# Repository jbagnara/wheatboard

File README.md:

# wheatboard

```bash
sudo pacman -Syu kicad
sudo pacman -Syu --asdeps kicad-library kicad-library-3d
```

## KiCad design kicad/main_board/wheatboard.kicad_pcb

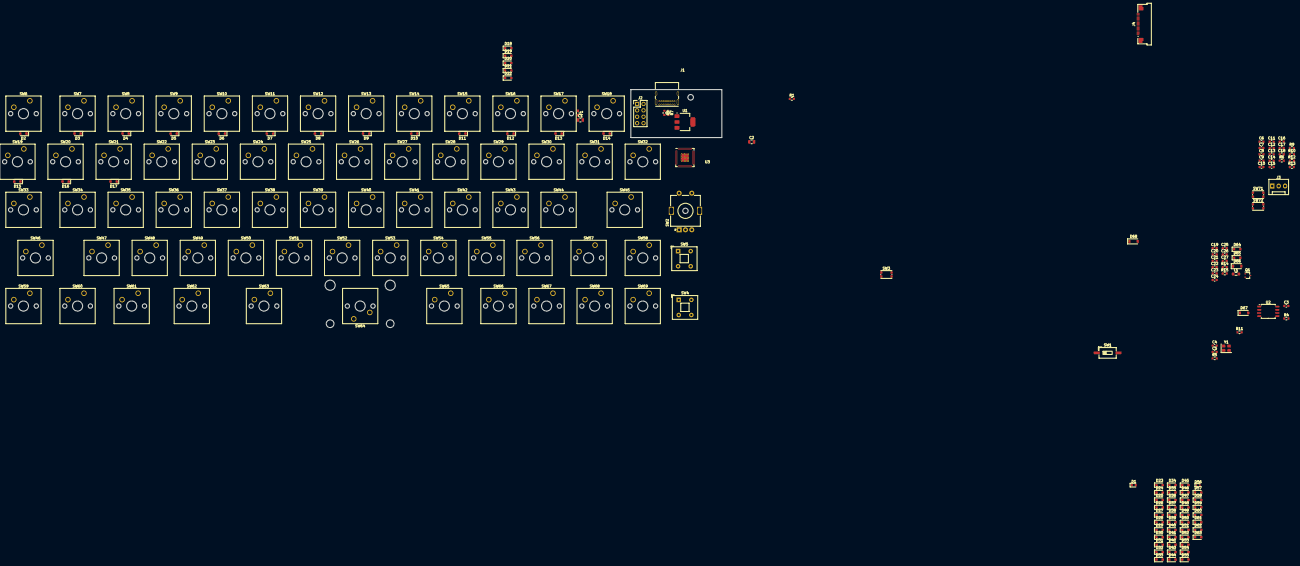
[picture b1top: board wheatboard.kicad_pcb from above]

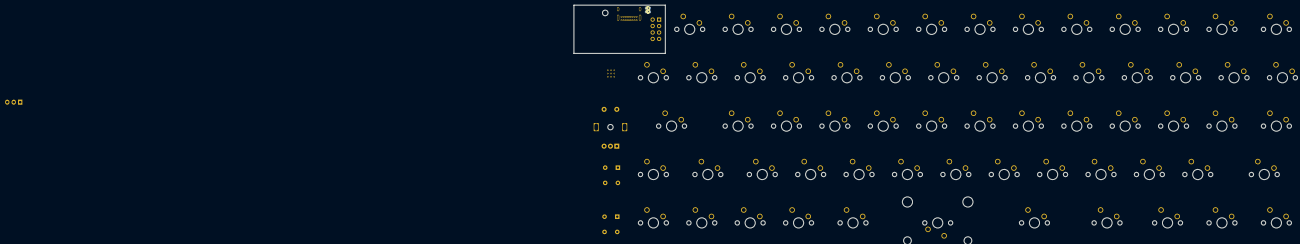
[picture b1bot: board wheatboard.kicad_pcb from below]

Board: 2 copper layers, 192 parts (2 on the bottom side), 132 nets, no tracks yet.

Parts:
C1, C2: 10u; C_0805_2012Metric
C3, C6, C7, C8, C9, C10, C11, C12, C13, C14, C17, C18: 100n; C_0603_1608Metric
C4, C5: 15p; C_0603_1608Metric
C15, C16, C19, C20, C21, C22, C23, C24, C26: 1u; C_0603_1608Metric
C25, C27: 4.7u; C_0603_1608Metric
D1: 3V3; LED_0603_1608Metric
D2, D3, D4, D5, D6, D7, D8, D9, D10, D11, D12, D13, D14, D15, D16, D17, D18, D19, D20, D21, D22, D23, D24, D25, D26, D27, D28, D29, D30, D31, D32, D33, D34, D35, D36, D37, D38, D39, D40, D41, D42, D43, D44, D45, D46, D47, D48, D49, D50, D51, D52, D53, D54, D55, D57, D58, D59, D60, D61, D62, D63, D64, D65: 1N4148WT; D_SOD-323_HandSoldering
D56: 1N4148WT; D_SOD-523
D66, D67, D68: MBR0530; D_SOD-123
F1: Fuse; Fuse_0603_1608Metric_Pad1.05x0.95mm_HandSolder
J1: USB_C_Receptacle_USB2.0_16P; USB_C_Receptacle_GCT_USB4085
J2: Conn_01x08; PinHeader_2x04_P2.54mm_Vertical
J3: SWD Debug; FanPinHeader_1x03_P2.54mm_Vertical
J4: Conn_01x18; Amphenol_F32Q-1A7x1-11018_1x18-1MP_P0.5mm_Horizontal
L1: 47u; L_0805_2012Metric_Pad1.05x1.20mm_HandSolder
Q1: Si1308EDL; SOT-323_SC-70
R1: 110; R_0603_1608Metric
R2, R3: 5.1k; R_0603_1608Metric
R4: DNF; R_0603_1608Metric
R5, R6: 1k; R_0603_1608Metric
R7, R8: 27; R_0603_1608Metric
R9, R10, R11, R12, R13: 10k; R_0603_1608Metric
R14: 1M; R_0603_1608Metric
R15: 2.2; R_0603_1608Metric
SW1: SW_DIP_x01; SW_DIP_SPSTx01_Slide_6.7x4.1mm_W8.61mm_P2.54mm_LowProfile
SW2: RotaryEncoder_Switch; RotaryEncoder_Alps_EC11E-Switch_Vertical_H20mm_MountingHoles
SW3, SW71, SW72: SW_Push; SW_Push_1P1T_NO_CK_KMR2
SW4: SW_Push; SW_Push_2P1T_Toggle_CK_PVA1xxH3xxxxxxV2
SW5: SW_Push; SW_Push_2P1T_Toggle_CK_PVA1xxH2xxxxxxV2
SW6, SW33, SW57, SW59, SW61, SW62, SW65: SW_Push; SW_Cherry_MX_1.25u_PCB
SW7, SW8, SW9, SW10, SW11, SW12, SW13, SW14, SW15, SW16, SW17, SW18, SW19, SW20, SW21, SW22, SW23, SW24, SW25, SW26, SW27, SW28, SW29, SW30, SW31, SW32, SW34, SW35, SW36, SW37, SW38, SW39, SW40, SW41, SW42, SW43, SW44, SW47, SW48, SW49, SW50, SW51, SW52, SW53, SW54, SW55, SW56, SW58, SW60, SW66, SW67, SW68, SW69: SW_Push; SW_Cherry_MX_1.00u_PCB
SW45, SW46, SW63: SW_Push; SW_Cherry_MX_1.75u_PCB
SW64: SW_Push; SW_Cherry_MX_2.25u_PCB
U1: NCP1117-3.3_SOT223; SOT-223-3_TabPin2
U2: W25Q128JVS; SOIC-8_5.3x5.3mm_P1.27mm
U3: RP2040; RP2040-QFN-56
Y1: ABM8-272-T3; Crystal_SMD_3225-4Pin_3.2x2.5mm

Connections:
+1V1: C6.1, C7.1, C15.1, U3.23 (DVDD), U3.45 (VREG_VOUT), U3.50 (DVDD)
+3V3: C2.1, C3.1, C8.1, C9.1, C10.1, C11.1, C12.1, C13.1, C14.1, C16.1, C27.1, J4.10, L1.1, R1.1, R4.1, R9.1, R10.1, R11.1, R12.1, R13.1, U1.2 (VO), U2.8 (VCC), U3.1 (IOVDD), U3.10 (IOVDD), U3.22 (IOVDD), U3.33 (IOVDD), U3.42 (IOVDD), U3.43 (ADC_AVDD), U3.44 (VREG_IN), U3.48 (USB_VDD), U3.49 (IOVDD)
/Flash/~USB_BOOT: R5.2, SW1.2
/MCU/RUN: R11.2, SW3.1, U3.26 (RUN)
/MCU/SWCLK: J3.3, U3.24 (SWCLK)
/MCU/SWD: J3.1, U3.25 (SWD)
Col0: D2.1 (K), D15.1 (K), D29.1 (K), D42.1 (K), D55.1 (K), U3.18 (GPIO15)
Col1: D3.1 (K), D16.1 (K), D30.1 (K), D56.1 (K), U3.17 (GPIO14)
Col2: D4.1 (K), D17.1 (K), D31.1 (K), D43.1 (K), D57.1 (K), U3.16 (GPIO13)
Col3: D5.1 (K), D18.1 (K), D32.1 (K), D44.1 (K), U3.15 (GPIO12)
Col4: D6.1 (K), D19.1 (K), D33.1 (K), D45.1 (K), D58.1 (K), U3.14 (GPIO11)
Col5: D7.1 (K), D20.1 (K), D34.1 (K), D46.1 (K), D59.1 (K), U3.13 (GPIO10)
Col6: D8.1 (K), D21.1 (K), D35.1 (K), D47.1 (K), U3.12 (GPIO9)
Col7: D9.1 (K), D22.1 (K), D36.1 (K), D48.1 (K), D60.1 (K), U3.11 (GPIO8)
Col8: D10.1 (K), D23.1 (K), D37.1 (K), D49.1 (K), U3.9 (GPIO7)
Col9: D11.1 (K), D24.1 (K), D38.1 (K), D50.1 (K), D61.1 (K), U3.8 (GPIO6)
Col10: D12.1 (K), D25.1 (K), D39.1 (K), D51.1 (K), D62.1 (K), U3.7 (GPIO5)
Col11: D13.1 (K), D26.1 (K), D40.1 (K), D52.1 (K), D63.1 (K), U3.6 (GPIO4)
Col12: D14.1 (K), D27.1 (K), D41.1 (K), D53.1 (K), D64.1 (K), U3.5 (GPIO3)
Col13: D28.1 (K), D54.1 (K), D65.1 (K), U3.4 (GPIO2)
DISPLAY_D/C: J4.6, U3.31 (GPIO20)
DISPLAY_GDR: J4.1, Q1.1 (G), R14.1
DISPLAY_PREVGH: C26.1, D68.1 (K), J4.15
DISPLAY_PREVGL: C24.1, D66.2 (A), J4.17
DISPLAY_RESE: J4.2, Q1.2 (S), R15.1
GND: C1.2, C2.2, C3.2, C4.2, C5.2, C6.2, C7.2, C8.2, C9.2, C10.2, C11.2, C12.2, C13.2, C14.2, C15.2, C16.2, C17.2, C18.2, C19.2, C20.1, C21.1, C22.1, C23.1, C24.2, C26.2, C27.2, D1.1 (K), D67.1 (K), J1.A1 (GND), J1.A12 (GND), J1.B1 (GND), J1.B12 (GND), J1.S1 (SHIELD), J3.2, J4.11, R2.2, R3.1, R14.2, R15.2, SW1.1, SW2.C, SW2.S2, SW3.2, SW4.2, SW5.2, SW71.2, SW72.2, U1.1 (GND), U2.4 (GND), U3.19 (TESTEN), U3.57 (GND), Y1.2, Y1.4
unnamed: C5.1, R6.2, Y1.3
unnamed: D1.2 (A), R1.2
unnamed: D2.2 (A), SW6.2
unnamed: D3.2 (A), SW7.2
unnamed: D4.2 (A), SW8.2
unnamed: D5.2 (A), SW9.2
unnamed: D6.2 (A), SW10.2
unnamed: D7.2 (A), SW11.2
unnamed: D8.2 (A), SW12.2
unnamed: D9.2 (A), SW13.2
unnamed: D10.2 (A), SW14.2
unnamed: D11.2 (A), SW15.2
unnamed: D12.2 (A), SW16.2
unnamed: D13.2 (A), SW17.2
unnamed: D14.2 (A), SW18.2
unnamed: D15.2 (A), SW19.2
unnamed: D16.2 (A), SW20.2
unnamed: D17.2 (A), SW21.2
unnamed: D18.2 (A), SW22.2
unnamed: D19.2 (A), SW23.2
unnamed: D20.2 (A), SW24.2
unnamed: D21.2 (A), SW25.2
unnamed: D22.2 (A), SW26.2
unnamed: D23.2 (A), SW27.2
unnamed: D24.2 (A), SW28.2
unnamed: D25.2 (A), SW29.2
unnamed: D26.2 (A), SW30.2
unnamed: D27.2 (A), SW31.2
unnamed: D28.2 (A), SW32.2
unnamed: D29.2 (A), SW33.2
unnamed: D30.2 (A), SW34.2
unnamed: D31.2 (A), SW35.2
unnamed: D32.2 (A), SW36.2
unnamed: D33.2 (A), SW37.2
unnamed: D34.2 (A), SW38.2
unnamed: D35.2 (A), SW39.2
unnamed: D36.2 (A), SW40.2
unnamed: D37.2 (A), SW41.2
unnamed: D38.2 (A), SW42.2
unnamed: D39.2 (A), SW43.2
unnamed: D40.2 (A), SW44.2
unnamed: D41.2 (A), SW45.2
unnamed: D42.2 (A), SW46.2
unnamed: D43.2 (A), SW47.2
unnamed: D44.2 (A), SW48.2
unnamed: D45.2 (A), SW49.2
unnamed: D46.2 (A), SW50.2
unnamed: D47.2 (A), SW51.2
unnamed: D48.2 (A), SW52.2
unnamed: D49.2 (A), SW53.2
unnamed: D50.2 (A), SW54.2
unnamed: D51.2 (A), SW55.2
unnamed: D52.2 (A), SW56.2
unnamed: D53.2 (A), SW57.2
unnamed: D54.2 (A), SW58.2
unnamed: D55.2 (A), SW59.2
unnamed: D56.2 (A), SW60.2
unnamed: D57.2 (A), SW61.2
unnamed: D58.2 (A), SW62.2
unnamed: D59.2 (A), SW63.2
unnamed: D60.2 (A), SW64.2
unnamed: D61.2 (A), SW65.2
unnamed: D62.2 (A), SW66.2
unnamed: D63.2 (A), SW67.2
unnamed: D64.2 (A), SW68.2
unnamed: D65.2 (A), SW69.2
unnamed: C25.1, D66.1 (K), D67.2 (A)
unnamed: C25.2, D68.2 (A), L1.2, Q1.3 (D)
unnamed: F1.1, J1.A4 (VBUS), J1.A9 (VBUS), J1.B4 (VBUS), J1.B9 (VBUS)
unnamed: J1.A5 (CC1), R2.1
unnamed: J1.B5 (CC2), R3.2
unnamed: J2.4, U3.30 (GPIO19)
unnamed: J2.5, U3.38 (GPIO26_ADC0)
unnamed: J2.6, U3.39 (GPIO27_ADC1)
unnamed: J2.7, U3.40 (GPIO28_ADC2)
unnamed: J2.8, U3.41 (GPIO29_ADC3)
unnamed: C19.1, J4.3
unnamed: C20.2, J4.12
unnamed: C21.2, J4.14
unnamed: C22.2, J4.16
unnamed: C23.2, J4.18
unnamed: R12.2, SW5.1
unnamed: R13.2, SW4.1
unnamed: C17.1, R9.2, SW2.A, U3.2 (GPIO0)
unnamed: C18.1, R10.2, SW2.B, U3.3 (GPIO1)
unnamed: R8.2, U3.46 (USB_DM)
unnamed: R7.2, U3.47 (USB_DP)
QSPI_SCLK: U2.6 (CLK), U3.52 (QSPI_SCLK)
QSPI_SD0: U2.5 (DI(IO0)), U3.53 (QSPI_SD0)
QSPI_SD1: U2.2 (DO(IO1)), U3.55 (QSPI_SD1)
QSPI_SD2: U2.3 (IO2), U3.54 (QSPI_SD2)
QSPI_SD3: U2.7 (IO3), U3.51 (QSPI_SD3)
QSPI_SS: R4.2, R5.1, U2.1 (~CS), U3.56 (QSPI_SS)
Row0: SW6.1, SW7.1, SW8.1, SW9.1, SW10.1, SW11.1, SW12.1, SW13.1, SW14.1, SW15.1, SW16.1, SW17.1, SW18.1, U3.37 (GPIO25)
Row1: SW19.1, SW20.1, SW21.1, SW22.1, SW23.1, SW24.1, SW25.1, SW26.1, SW27.1, SW28.1, SW29.1, SW30.1, SW31.1, SW32.1, U3.36 (GPIO24)
Row2: SW33.1, SW34.1, SW35.1, SW36.1, SW37.1, SW38.1, SW39.1, SW40.1, SW41.1, SW42.1, SW43.1, SW44.1, SW45.1, U3.35 (GPIO23)
Row3: SW46.1, SW47.1, SW48.1, SW49.1, SW50.1, SW51.1, SW52.1, SW53.1, SW54.1, SW55.1, SW56.1, SW57.1, SW58.1, U3.34 (GPIO22)
Row4: SW59.1, SW60.1, SW61.1, SW62.1, SW63.1, SW64.1, SW65.1, SW66.1, SW67.1, SW68.1, SW69.1, U3.32 (GPIO21)
SPI_CS0: J2.3, U3.29 (GPIO18)
SPI_MOSI: J2.1, J4.9, U3.27 (GPIO16)
SPI_SCK: J2.2, J4.8, U3.28 (GPIO17)
USB_D+: J1.A6 (D+), J1.B6 (D+), R7.1
USB_D-: J1.A7 (D-), J1.B7 (D-), R8.1
VBUS: C1.1, F1.2, U1.3 (VI)
XIN: C4.1, U3.20 (XIN), Y1.1
XOUT: R6.1, U3.21 (XOUT)

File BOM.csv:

"Reference","Value","Datasheet","Footprint","Qty","DNP"
"C1,C2",10u,https://www.mouser.com/ProductDetail/Murata-Electronics/GRM1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,Capacitor_SMD:C_0805_2012Metric,2,
"C3,C6,C7,C8,C9,C10,C11,C12,C13,C14","100n","https://www.mouser.com/ProductDetail/Vishay-Vitramon/VJ0603D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","Capacitor_SMD:C_0603_1608Metric","10",""
"C4,C5","15p","~","Capacitor_SMD:C_0603_1608Metric","2",""
"C15,C16",1u,https://www.mouser.com/ProductDetail/Murata-Electronics/GRM1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,Capacitor_SMD:C_0402_1005Metric,2,
"D1,D2,D3,D4,D5,D6,D7,D8,D9,D10,D11,D12,D13,D14,D15,D16,D17,D18,D19,D20,D21,D22,D23,D24,D25,D26,D27,D28,D29,D30,D31,D32,D33,D34,D35,D36,D37,D38,D39,D40,D41,D42,D43,D44,D45,D46,D47,D48,D49,D50,D51,D52,D53,D54,D55,D56,D57,D58,D59,D60,D61,D62,D63,D64,D65,D66,D69,D70","1N4148WT","https://www.diodes.com/assets/Datasheets/ds30396.pdf","Diode_SMD:D_SOD-523","68",""
"D67,D68",3V3,https://www.mouser.com/ProductDetail/Broadcom-Avago/ASCKCG00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,LED_SMD:LED_0603_1608Metric,2,
"F1","Fuse","~","Fuse:Fuse_0603_1608Metric_Pad1.05x0.95mm_HandSolder","1",""
"J1",USB_C_Receptacle_USB2.0_16P,https://www.mouser.com/ProductDetail/640-USB4085-GF-A,Connector_USB:USB_C_Receptacle_GCT_USB4085,1,
"J2",GPIO Breakout,https://www.mouser.com/ProductDetail/Harwin/M20-9990645?qs=J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,Connector_PinHeader_2.54mm:PinHeader_1x03_P2.54mm_Vertical,1,
"J3",SWD Debug,https://www.mouser.com/ProductDetail/Harwin/M20-9990645?qs=J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,Connector:FanPinHeader_1x03_P2.54mm_Vertical,1,
"R1,R2",5.1k,https://www.mouser.com/ProductDetail/Vishay-Dale/CRCW06035K1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,Resistor_SMD:R_0603,2,
"R3",DNF,~,Resistor_SMD:R_0603,1,
"R4,R5",1k,https://www.mouser.com/ProductDetail/Vishay-Dale/CRCW0603110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,Resistor_SMD:R_0603,2,
"R6,R7",27,https://www.mouser.com/ProductDetail/Vishay-Dale/CRCW060327R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,Resistor_SMD:R_0603,2,
"R8","10k","https://www.mouser.com/ProductDetail/Murata-Electronics/GRM1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","Resistor_SMD:R_0603_1608Metric","1",""
"R11,R12",110,https://www.mouser.com/ProductDetail/Vishay-Dale/CRCW0603110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,Resistor_SMD:R_0603,2,
"SW1","SW_DIP_x01","~","Button_Switch_SMD:SW_DIP_SPSTx01_Slide_6.7x4.1mm_W8.61mm_P2.54mm_LowProfile","1",""
"SW3,SW4,SW5,SW6,SW7,SW8,SW9,SW10,SW11,SW12,SW13,SW14,SW15,SW16,SW17,SW18,SW19,SW20,SW21,SW22,SW23,SW24,SW25,SW26,SW27,SW28,SW29,SW30,SW31,SW32,SW33,SW34,SW35,SW36,SW37,SW38,SW39,SW40,SW41,SW42,SW43,SW44,SW45,SW46,SW47,SW48,SW49,SW50,SW51,SW52,SW53,SW54,SW55,SW56,SW57,SW58,SW59,SW60,SW61,SW62,SW63,SW64,SW65,SW66,SW67,SW68,SW69,SW70","SW_Push","~","Button_Switch_Keyboard:SW_Cherry_MX_1.00u_PCB,Button_Switch_Keyboard:SW_Cherry_MX_1.25u_PCB,Button_Switch_Keyboard:SW_Cherry_MX_1.50u_PCB,Button_Switch_Keyboard:SW_Cherry_MX_2.25u_PCB,Button_Switch_Keyboard:SW_Cherry_MX_6.25u_PCB,Button_Switch_SMD:SW_Push_1P1T_NO_CK_KMR2,PCM_Switch_Keyboard_Cherry_MX:SW_Cherry_MX_Plate_1.75u","69",""
"U1",NCP1117-3.3_SOT223,https://www.mouser.com/ProductDetail/863-NCP1117ST33T3G,Package_TO_SOT_SMD:SOT-223-3_TabPin2,1,
"U2",W25Q128JVS,http://www.winbond.com/resource-files/w25q128jv_dtr%20revc%2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,Package_SO:SOIC-8_5.23x5.23mm_P1.27mm,1,
"U3",RP2040,https://www.mouser.com/ProductDetail/Raspberry-Pi/SC091413?q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,RP2040_minimal_r2:RP2040-QFN-56,1,
"Y1",ABM8-272-T3,https://www.mouser.com/ProductDetail/ABRACON/ABM8-272-T3?qs=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,Crystal:Crystal_SMD_3225-4Pin_3.2x2.5mm,1,
"SW2",SW_Push,https://www.mouser.com/ProductDetail/611-KMR231GLFS,Pushbutton Switch,1,

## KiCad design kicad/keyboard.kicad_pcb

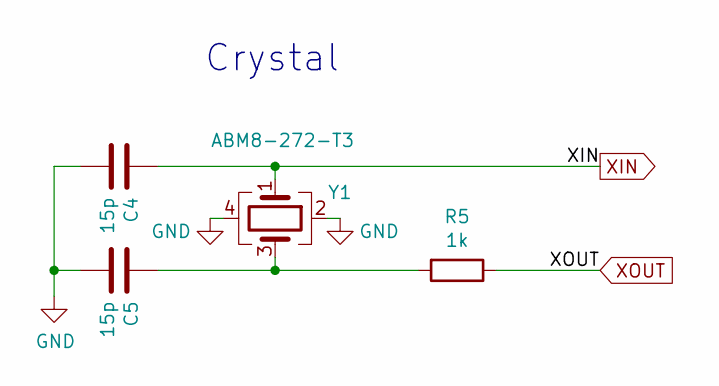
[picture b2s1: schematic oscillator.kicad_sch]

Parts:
C4, C5: 15p; C_0603_1608Metric
R5: 1k; R_0603_1608Metric
Y1: ABM8-272-T3; Crystal_SMD_3225-4Pin_3.2x2.5mm

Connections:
GND: C4.2, C5.2, Y1.2, Y1.4; also elsewhere on the board
unnamed: C5.1, R5.2, Y1.3
XIN: C4.1, Y1.1; also elsewhere on the board
XOUT: R5.1; also elsewhere on the board

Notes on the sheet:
Crystal

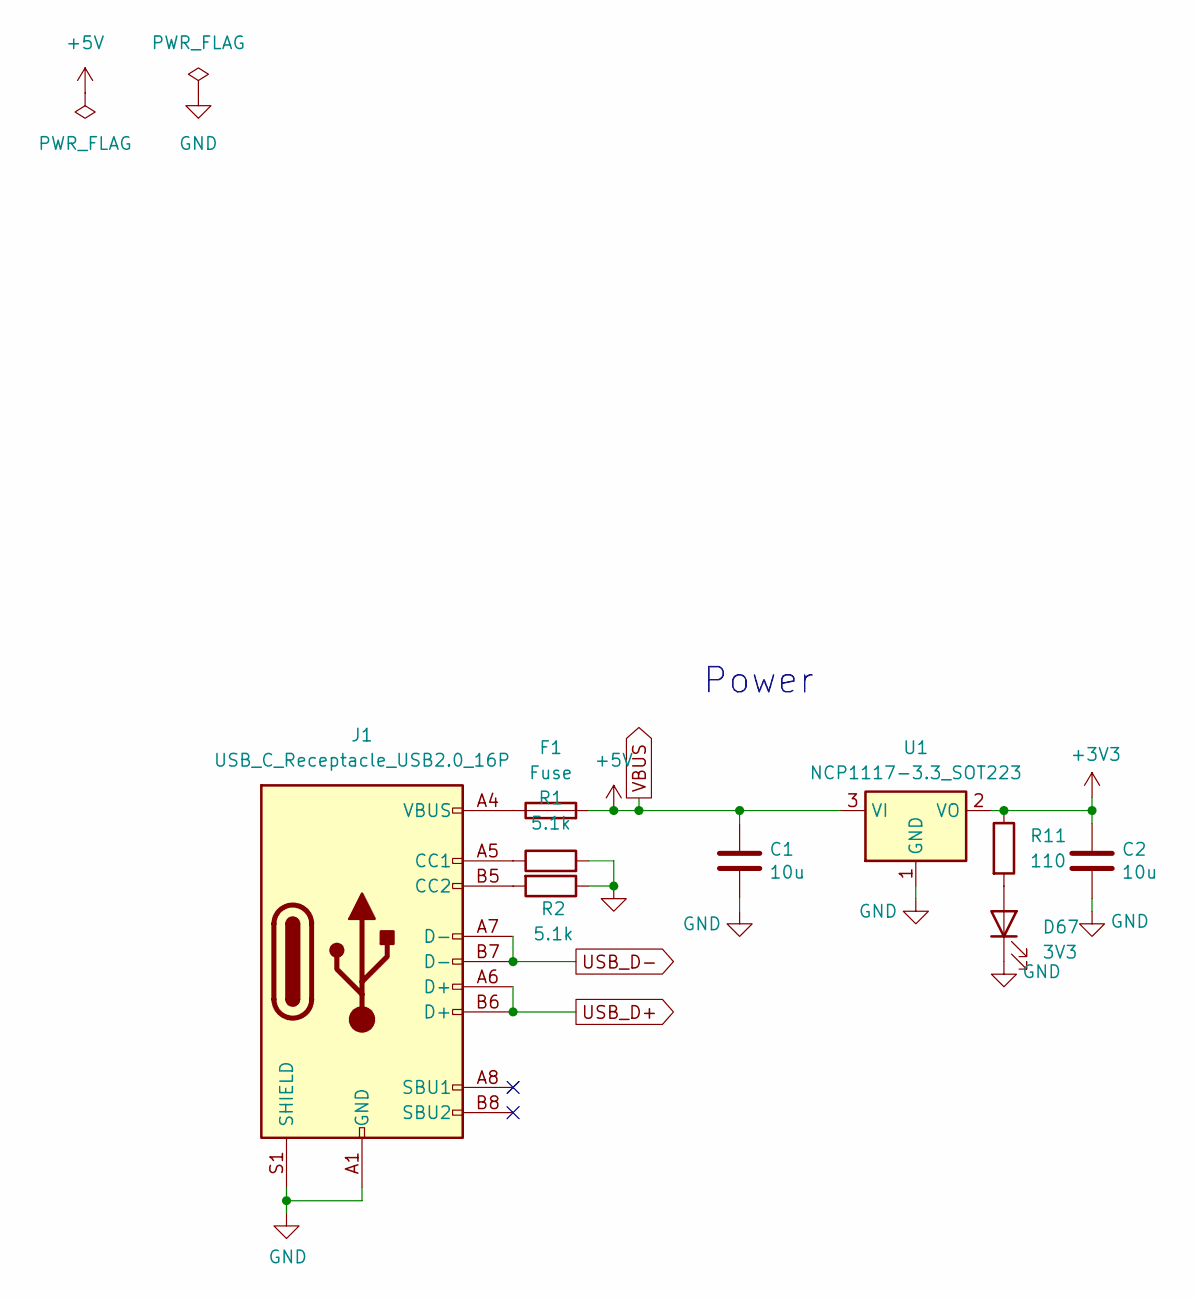
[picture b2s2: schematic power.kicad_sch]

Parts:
C1, C2: 10u; C_0805_2012Metric
D67: 3V3; LED_0603_1608Metric
F1: Fuse; Fuse_0603_1608Metric_Pad1.05x0.95mm_HandSolder
J1: USB_C_Receptacle_USB2.0_16P; USB_C_Receptacle_GCT_USB4085
R1, R2: 5.1k; R_0603_1608Metric
R11: 110; R_0603_1608Metric
U1: NCP1117-3.3_SOT223; SOT-223-3_TabPin2

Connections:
+3V3: C2.1, R11.1, U1.2 (VO); also elsewhere on the board
GND: C1.2, C2.2, D67.1 (K), J1.A1 (GND), J1.A12 (GND), J1.B1 (GND), J1.B12 (GND), J1.S1 (SHIELD), R1.2, R2.1, U1.1 (GND); also elsewhere on the board
unnamed: D67.2 (A), R11.2
unnamed: F1.1, J1.A4 (VBUS), J1.A9 (VBUS), J1.B4 (VBUS), J1.B9 (VBUS)
unnamed: J1.A5 (CC1), R1.1
unnamed: J1.B5 (CC2), R2.2
USB_D+: J1.A6 (D+), J1.B6 (D+); also elsewhere on the board
USB_D-: J1.A7 (D-), J1.B7 (D-); also elsewhere on the board
VBUS: C1.1, F1.2, U1.3 (VI)

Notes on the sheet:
Power

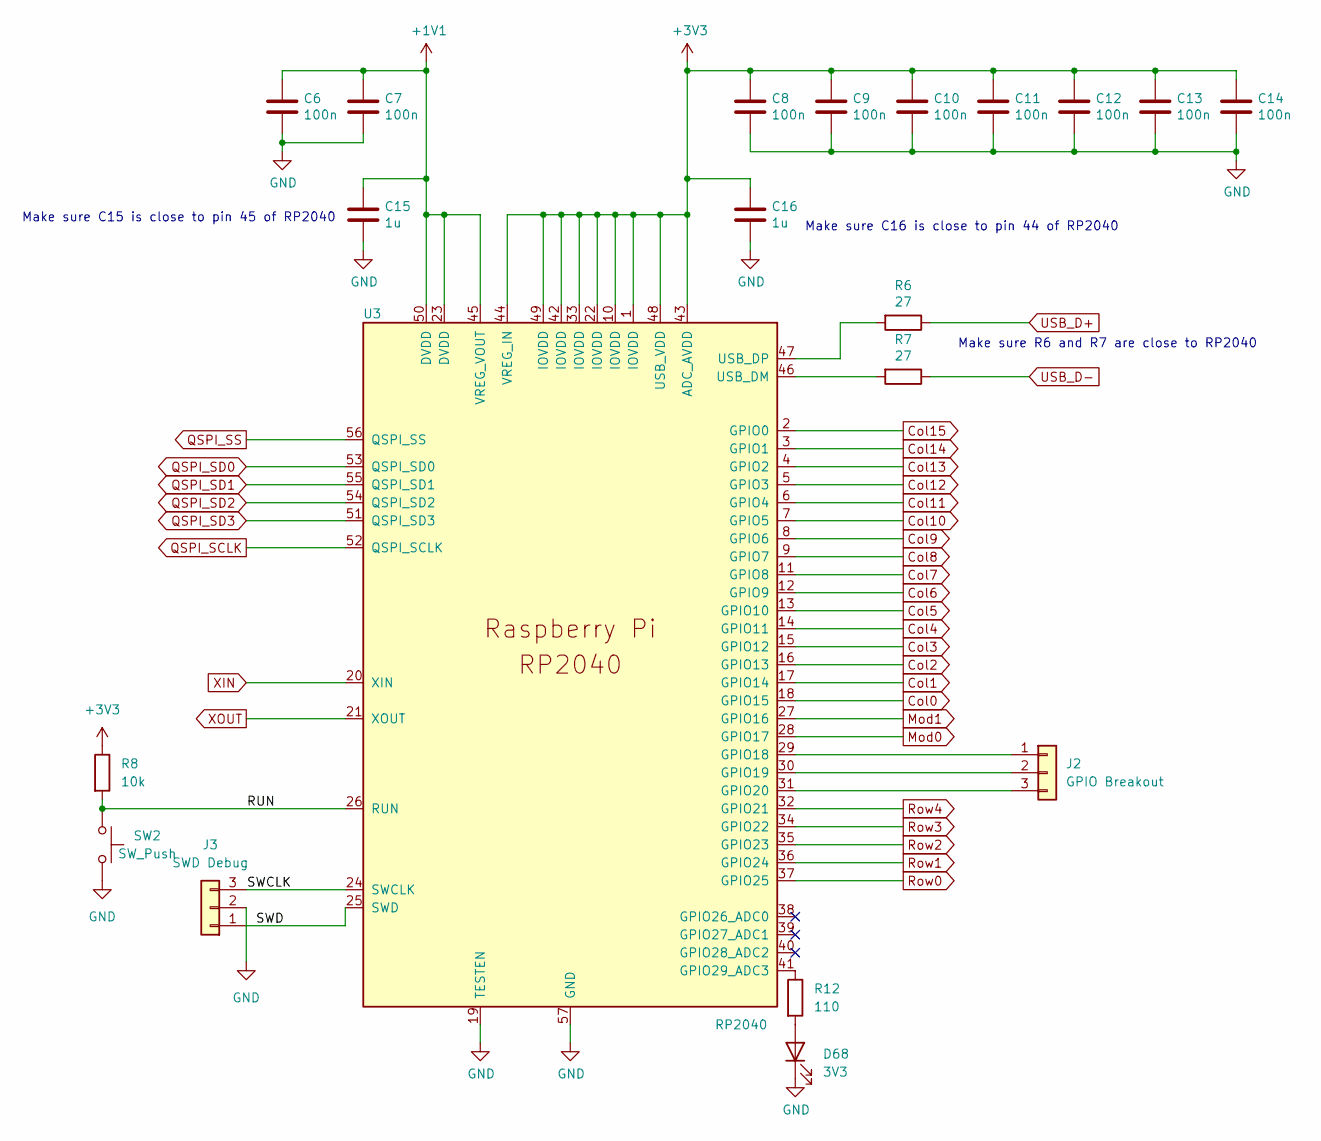
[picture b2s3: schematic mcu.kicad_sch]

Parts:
C6, C7, C8, C9, C10, C11, C12, C13, C14: 100n; C_0603_1608Metric
C15, C16: 1u; C_0603_1608Metric
D68: 3V3; LED_0603_1608Metric
J2: GPIO Breakout; PinHeader_1x03_P2.54mm_Vertical
J3: SWD Debug; FanPinHeader_1x03_P2.54mm_Vertical
R6, R7: 27; R_0603_1608Metric
R8: 10k; R_0603_1608Metric
R12: 110; R_0603_1608Metric
SW2: SW_Push; SW_Push_1P1T_NO_CK_KMR2
U3: RP2040; RP2040-QFN-56

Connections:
+1V1: C6.1, C7.1, C15.1, U3.23 (DVDD), U3.45 (VREG_VOUT), U3.50 (DVDD)
+3V3: C8.1, C9.1, C10.1, C11.1, C12.1, C13.1, C14.1, C16.1, R8.1, U3.1 (IOVDD), U3.10 (IOVDD), U3.22 (IOVDD), U3.33 (IOVDD), U3.42 (IOVDD), U3.43 (ADC_AVDD), U3.44 (VREG_IN), U3.48 (USB_VDD), U3.49 (IOVDD); also elsewhere on the board
/MCU/RUN: R8.2, SW2.1, U3.26 (RUN)
/MCU/SWCLK: J3.3, U3.24 (SWCLK)
/MCU/SWD: J3.1, U3.25 (SWD)
Col0: U3.18 (GPIO15); also elsewhere on the board
Col1: U3.17 (GPIO14); also elsewhere on the board
Col2: U3.16 (GPIO13); also elsewhere on the board
Col3: U3.15 (GPIO12); also elsewhere on the board
Col4: U3.14 (GPIO11); also elsewhere on the board
Col5: U3.13 (GPIO10); also elsewhere on the board
Col6: U3.12 (GPIO9); also elsewhere on the board
Col7: U3.11 (GPIO8); also elsewhere on the board
Col8: U3.9 (GPIO7); also elsewhere on the board
Col9: U3.8 (GPIO6); also elsewhere on the board
Col10: U3.7 (GPIO5); also elsewhere on the board
Col11: U3.6 (GPIO4); also elsewhere on the board
Col12: U3.5 (GPIO3); also elsewhere on the board
Col13: U3.4 (GPIO2); also elsewhere on the board
Col14: U3.3 (GPIO1); also elsewhere on the board
Col15: U3.2 (GPIO0); also elsewhere on the board
GND: C6.2, C7.2, C8.2, C9.2, C10.2, C11.2, C12.2, C13.2, C14.2, C15.2, C16.2, D68.1 (K), J3.2, SW2.2, U3.19 (TESTEN), U3.57 (GND); also elsewhere on the board
Mod0: U3.28 (GPIO17)
Mod1: U3.27 (GPIO16)
unnamed: D68.2 (A), R12.2
unnamed: J2.1, U3.29 (GPIO18)
unnamed: J2.2, U3.30 (GPIO19)
unnamed: J2.3, U3.31 (GPIO20)
unnamed: R12.1, U3.41 (GPIO29_ADC3)
unnamed: R7.2, U3.46 (USB_DM)
unnamed: R6.2, U3.47 (USB_DP)
QSPI_SCLK: U3.52 (QSPI_SCLK); also elsewhere on the board
QSPI_SD0: U3.53 (QSPI_SD0); also elsewhere on the board
QSPI_SD1: U3.55 (QSPI_SD1); also elsewhere on the board
QSPI_SD2: U3.54 (QSPI_SD2); also elsewhere on the board
QSPI_SD3: U3.51 (QSPI_SD3); also elsewhere on the board
QSPI_SS: U3.56 (QSPI_SS); also elsewhere on the board
Row0: U3.37 (GPIO25); also elsewhere on the board
Row1: U3.36 (GPIO24); also elsewhere on the board
Row2: U3.35 (GPIO23); also elsewhere on the board
Row3: U3.34 (GPIO22); also elsewhere on the board
Row4: U3.32 (GPIO21); also elsewhere on the board
USB_D+: R6.1; also elsewhere on the board
USB_D-: R7.1; also elsewhere on the board
XIN: U3.20 (XIN); also elsewhere on the board
XOUT: U3.21 (XOUT); also elsewhere on the board

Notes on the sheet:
Make sure C16 is close to pin 44 of RP2040
Make sure C15 is close to pin 45 of RP2040
Make sure R6 and R7 are close to RP2040

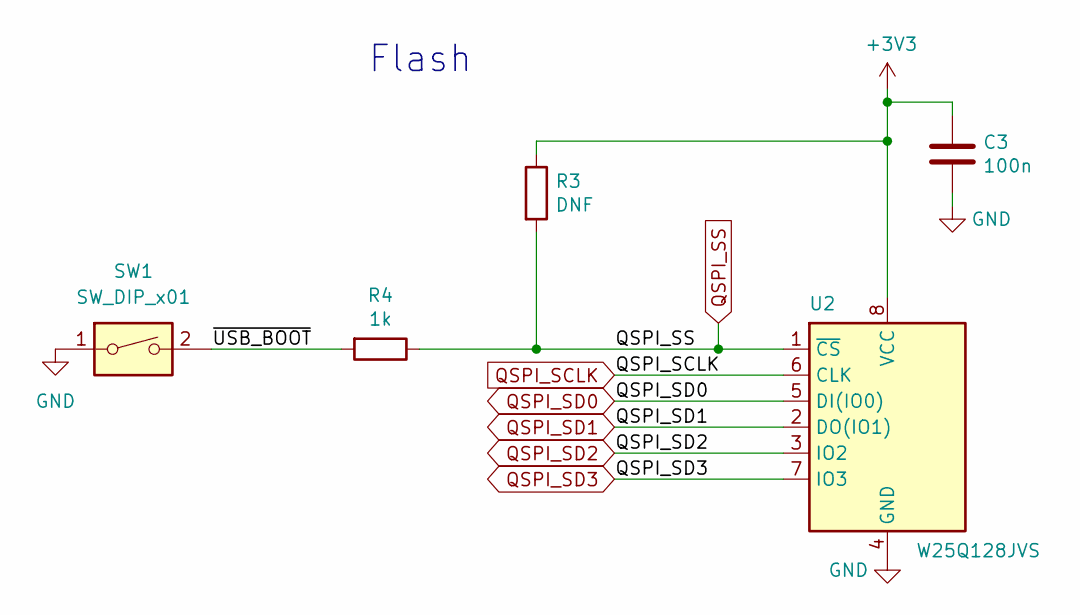
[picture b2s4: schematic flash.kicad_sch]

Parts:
C3: 100n; C_0603_1608Metric
R3: DNF; R_0603_1608Metric
R4: 1k; R_0603_1608Metric
SW1: SW_DIP_x01; SW_DIP_SPSTx01_Slide_6.7x4.1mm_W8.61mm_P2.54mm_LowProfile
U2: W25Q128JVS; SOIC-8_5.23x5.23mm_P1.27mm

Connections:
+3V3: C3.1, R3.1, U2.8 (VCC); also elsewhere on the board
/Flash/~USB_BOOT: R4.2, SW1.2
GND: C3.2, SW1.1, U2.4 (GND); also elsewhere on the board
QSPI_SCLK: U2.6 (CLK); also elsewhere on the board
QSPI_SD0: U2.5 (DI(IO0)); also elsewhere on the board
QSPI_SD1: U2.2 (DO(IO1)); also elsewhere on the board
QSPI_SD2: U2.3 (IO2); also elsewhere on the board
QSPI_SD3: U2.7 (IO3); also elsewhere on the board
QSPI_SS: R3.2, R4.1, U2.1 (~CS); also elsewhere on the board

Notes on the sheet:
Flash

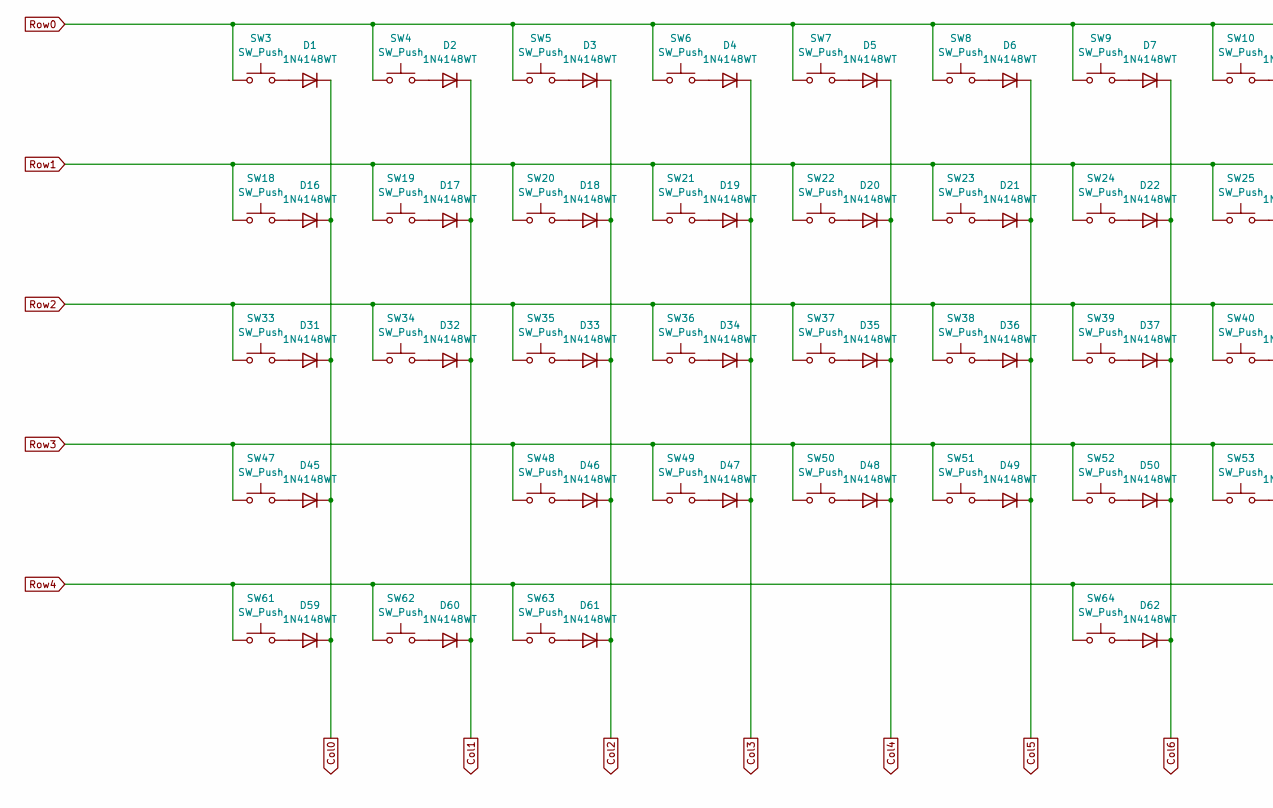
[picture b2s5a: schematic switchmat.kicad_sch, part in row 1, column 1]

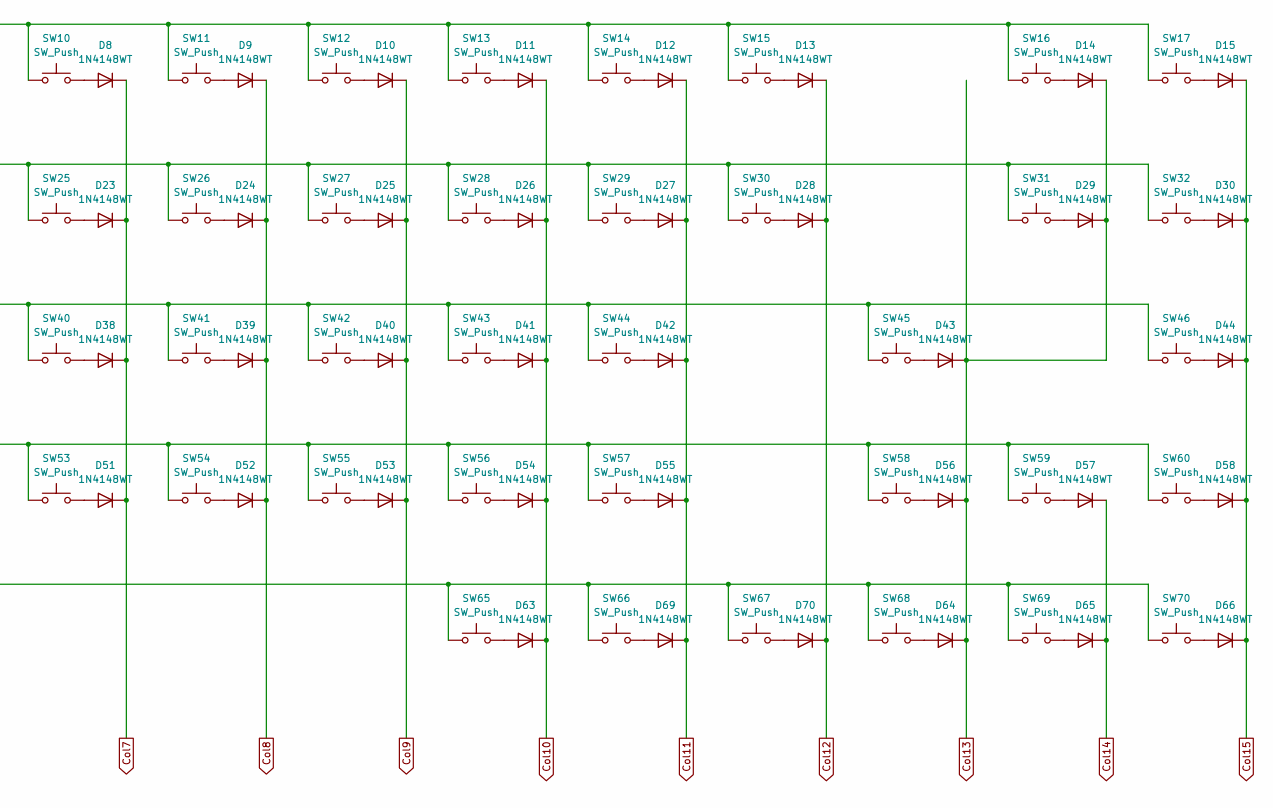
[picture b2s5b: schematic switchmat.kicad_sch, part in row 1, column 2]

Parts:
D1, D2, D3, D4, D5, D6, D7, D8, D9, D10, D11, D12, D13, D14, D15, D16, D17, D18, D19, D20, D21, D22, D23, D24, D25, D26, D27, D28, D29, D30, D31, D32, D33, D34, D35, D36, D37, D38, D39, D40, D41, D42, D43, D44, D45, D46, D47, D48, D49, D50, D51, D52, D53, D54, D55, D56, D57, D58, D59, D60, D61, D62, D63, D64, D65, D66, D69, D70: 1N4148WT; D_SOD-523
SW3, SW4, SW5, SW6, SW7, SW8, SW9, SW10, SW11, SW12, SW13, SW14, SW15, SW16, SW17, SW19, SW20, SW21, SW22, SW23, SW24, SW25, SW26, SW27, SW28, SW29, SW30, SW31, SW32, SW34, SW35, SW36, SW37, SW38, SW39, SW40, SW41, SW42, SW43, SW44, SW46, SW48, SW49, SW50, SW51, SW52, SW53, SW54, SW55, SW56, SW57, SW59, SW60, SW65, SW66, SW67, SW68, SW69, SW70: SW_Push; SW_Cherry_MX_1.00u_PCB
SW18: SW_Push; SW_Cherry_MX_1.50u_PCB
SW33, SW58: SW_Push; SW_Cherry_MX_Plate_1.75u
SW45, SW47: SW_Push; SW_Cherry_MX_2.25u_PCB
SW61, SW62, SW63: SW_Push; SW_Cherry_MX_1.25u_PCB
SW64: SW_Push; SW_Cherry_MX_6.25u_PCB

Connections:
Col0: D1.1 (K), D16.1 (K), D31.1 (K), D45.1 (K), D59.1 (K); also elsewhere on the board
Col1: D2.1 (K), D17.1 (K), D32.1 (K), D60.1 (K); also elsewhere on the board
Col2: D3.1 (K), D18.1 (K), D33.1 (K), D46.1 (K), D61.1 (K); also elsewhere on the board
Col3: D4.1 (K), D19.1 (K), D34.1 (K), D47.1 (K); also elsewhere on the board
Col4: D5.1 (K), D20.1 (K), D35.1 (K), D48.1 (K); also elsewhere on the board
Col5: D6.1 (K), D21.1 (K), D36.1 (K), D49.1 (K); also elsewhere on the board
Col6: D7.1 (K), D22.1 (K), D37.1 (K), D50.1 (K), D62.1 (K); also elsewhere on the board
Col7: D8.1 (K), D23.1 (K), D38.1 (K), D51.1 (K); also elsewhere on the board
Col8: D9.1 (K), D24.1 (K), D39.1 (K), D52.1 (K); also elsewhere on the board
Col9: D10.1 (K), D25.1 (K), D40.1 (K), D53.1 (K); also elsewhere on the board
Col10: D11.1 (K), D26.1 (K), D41.1 (K), D54.1 (K), D63.1 (K); also elsewhere on the board
Col11: D12.1 (K), D27.1 (K), D42.1 (K), D55.1 (K), D69.1 (K); also elsewhere on the board
Col12: D13.1 (K), D28.1 (K), D70.1 (K); also elsewhere on the board
Col13: D14.1 (K), D29.1 (K), D43.1 (K), D56.1 (K), D64.1 (K); also elsewhere on the board
Col14: D57.1 (K), D65.1 (K); also elsewhere on the board
Col15: D15.1 (K), D30.1 (K), D44.1 (K), D58.1 (K), D66.1 (K); also elsewhere on the board
unnamed: D1.2 (A), SW3.2
unnamed: D2.2 (A), SW4.2
unnamed: D3.2 (A), SW5.2
unnamed: D4.2 (A), SW6.2
unnamed: D5.2 (A), SW7.2
unnamed: D6.2 (A), SW8.2
unnamed: D7.2 (A), SW9.2
unnamed: D8.2 (A), SW10.2
unnamed: D9.2 (A), SW11.2
unnamed: D10.2 (A), SW12.2
unnamed: D11.2 (A), SW13.2
unnamed: D12.2 (A), SW14.2
unnamed: D13.2 (A), SW15.2
unnamed: D14.2 (A), SW16.2
unnamed: D15.2 (A), SW17.2
unnamed: D16.2 (A), SW18.2
unnamed: D17.2 (A), SW19.2
unnamed: D18.2 (A), SW20.2
unnamed: D19.2 (A), SW21.2
unnamed: D20.2 (A), SW22.2
unnamed: D21.2 (A), SW23.2
unnamed: D22.2 (A), SW24.2
unnamed: D23.2 (A), SW25.2
unnamed: D24.2 (A), SW26.2
unnamed: D25.2 (A), SW27.2
unnamed: D26.2 (A), SW28.2
unnamed: D27.2 (A), SW29.2
unnamed: D28.2 (A), SW30.2
unnamed: D29.2 (A), SW31.2
unnamed: D30.2 (A), SW32.2
unnamed: D31.2 (A), SW33.2
unnamed: D32.2 (A), SW34.2
unnamed: D33.2 (A), SW35.2
unnamed: D34.2 (A), SW36.2
unnamed: D35.2 (A), SW37.2
unnamed: D36.2 (A), SW38.2
unnamed: D37.2 (A), SW39.2
unnamed: D38.2 (A), SW40.2
unnamed: D39.2 (A), SW41.2
unnamed: D40.2 (A), SW42.2
unnamed: D41.2 (A), SW43.2
unnamed: D42.2 (A), SW44.2
unnamed: D43.2 (A), SW45.2
unnamed: D44.2 (A), SW46.2
unnamed: D45.2 (A), SW47.2
unnamed: D46.2 (A), SW48.2
unnamed: D47.2 (A), SW49.2
unnamed: D48.2 (A), SW50.2
unnamed: D49.2 (A), SW51.2
unnamed: D50.2 (A), SW52.2
unnamed: D51.2 (A), SW53.2
unnamed: D52.2 (A), SW54.2
unnamed: D53.2 (A), SW55.2
unnamed: D54.2 (A), SW56.2
unnamed: D55.2 (A), SW57.2
unnamed: D56.2 (A), SW58.2
unnamed: D57.2 (A), SW59.2
unnamed: D58.2 (A), SW60.2
unnamed: D59.2 (A), SW61.2
unnamed: D60.2 (A), SW62.2
unnamed: D61.2 (A), SW63.2
unnamed: D62.2 (A), SW64.2
unnamed: D63.2 (A), SW65.2
unnamed: D64.2 (A), SW68.2
unnamed: D65.2 (A), SW69.2
unnamed: D66.2 (A), SW70.2
unnamed: D69.2 (A), SW66.2
unnamed: D70.2 (A), SW67.2
Row0: SW3.1, SW4.1, SW5.1, SW6.1, SW7.1, SW8.1, SW9.1, SW10.1, SW11.1, SW12.1, SW13.1, SW14.1, SW15.1, SW16.1, SW17.1; also elsewhere on the board
Row1: SW18.1, SW19.1, SW20.1, SW21.1, SW22.1, SW23.1, SW24.1, SW25.1, SW26.1, SW27.1, SW28.1, SW29.1, SW30.1, SW31.1, SW32.1; also elsewhere on the board
Row2: SW33.1, SW34.1, SW35.1, SW36.1, SW37.1, SW38.1, SW39.1, SW40.1, SW41.1, SW42.1, SW43.1, SW44.1, SW45.1, SW46.1; also elsewhere on the board
Row3: SW47.1, SW48.1, SW49.1, SW50.1, SW51.1, SW52.1, SW53.1, SW54.1, SW55.1, SW56.1, SW57.1, SW58.1, SW59.1, SW60.1; also elsewhere on the board
Row4: SW61.1, SW62.1, SW63.1, SW64.1, SW65.1, SW66.1, SW67.1, SW68.1, SW69.1, SW70.1; also elsewhere on the board

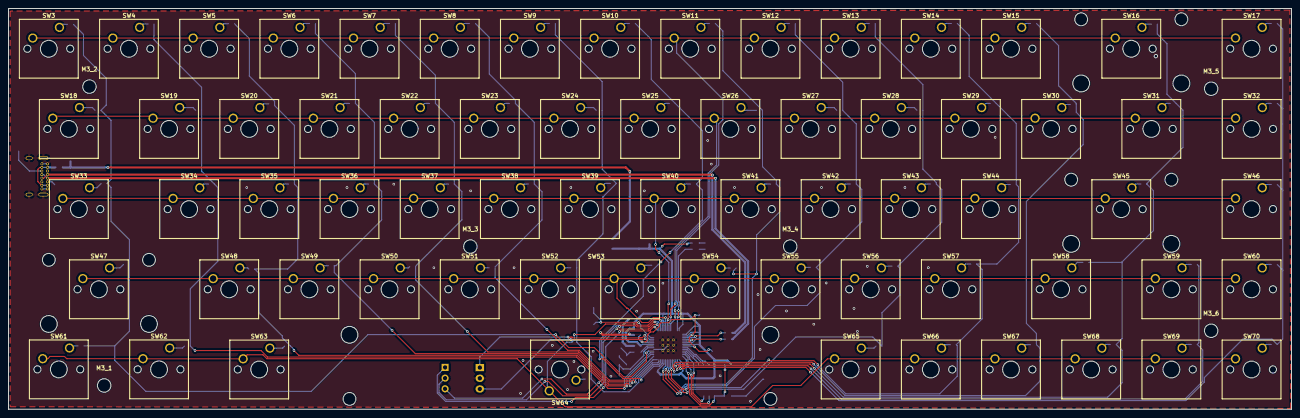
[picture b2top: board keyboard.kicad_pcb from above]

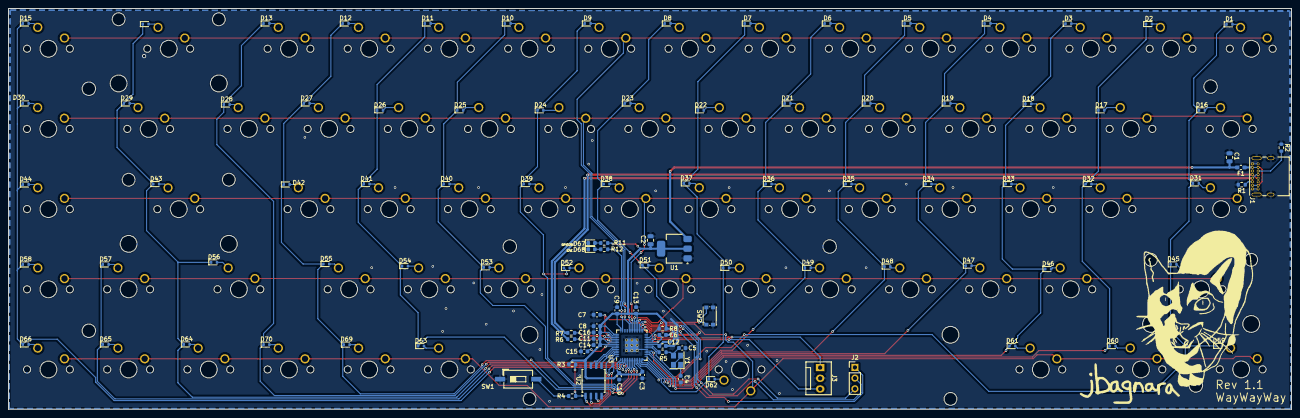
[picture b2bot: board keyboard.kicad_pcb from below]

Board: 2 copper layers, 304.8 x 95.2 mm, 180 parts (106 on the bottom side), 119 nets.

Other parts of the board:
M3_1, M3_2, M3_3, M3_4, M3_5, M3_6: MountingHole_3.2mm_M3

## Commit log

2025-07-31 add kicad files
2025-07-31 add parts list
2025-07-31 fix number of switches
2025-08-03 add script to allow flashing without second keyboard
2025-08-03 add vim mac and a macro
2025-08-11 add images
2025-08-16 actual attempt at source controlling kicad project
2025-08-17 moving things around
2025-08-23 separate main board and daughter board
2025-08-23 update keymap
